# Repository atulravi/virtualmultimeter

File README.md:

# Virtual Voltmeter

A RPI Pico and/or Arduino and Python based ecosystem that will make a virtual voltmeter appear on screen that updates real time and can be used by streamers  who wish to show voltages on the screen as well. 

Best Suited for hardware development streamers and content creators. 

The voltmeter cannot read reverse polarity and voltages >25 volts right now because of the resistor divider used. Feel free to hack at the device and code if ambitious. I have used the arduino based voltage detector modules that have a 30K and 7.5K resistor ladder.

# Hardware.
- Upload code to your favorite dev board with Serial communication capabilities. (code in /hardware)
(Tested with Arduino and RPI Pico)
- Connect the parts as described in the schematic in the /hardware folder. 
- Fit in enclosure that you can 3d print (files provided for 2 styles in /hardware )
- Enjoy. 
- Download the 3D Files either from the folder or from printables: https://www.printables.com/model/497685-voltmeter-with-a-pi-pico-that-casts-the-data-to-a-

# Software
- Download the setup.exe file from the v1.0.0 Release. (Check releases tab.)
- Finish the setup (Don't worry. Does not contain any viruses. Just python code that scans the serial port to give a o/p)
- In the startup page, type the com port the voltmeter is connected to as is (eg: COM3 (or) com3)
- Enjoy

# Setting up streaming with software
- (Tested with OBS only)
- Start the voltameter software. 
- Start OBS.
- Add a source
- Add a window capture
- Choose the virtual multimeter from the dropdown
- [scanning.exe]: vIRTUAL MULTIMETER ESCcrasci
- After setting it at the posistion of choice
- Right click on the multimeter scene in OBS and presws on filters
- Press on the + and add chroma key
- Choose custom key colour type
- Select colour and add HTML code #00FFFF
- Once done, save and you are good to go. 
- It will look somewhat like this

SEE VIDEO BELOW FOR COMPLETE SETUP

https://github.com/atulravi/virtualmultimeter/assets/70395057/c0b2f832-0102-4875-b9c9-df2db2375dfc

# Platform

# Device pictures:
Please note that the inline socket version that can be directly plugged into a multimeter is still in development and will be released soon. Until then, either frankenstien it in the multimeter of your choice, or add a 7 segment display and use it as a seperate device.
- PostBox enclosure type

# Frankenstiend in to a DMM

(BEWARE. IF YOU RUIN YOUR DMM, I TAKE NO RESPONSIBILITY. RISKS ARE INVOLVED WITH OSSH)

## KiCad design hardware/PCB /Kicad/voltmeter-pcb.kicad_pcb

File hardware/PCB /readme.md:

Note that these PCBs are not compatible with the 3D Enclosures provided. Do keep that in mind.

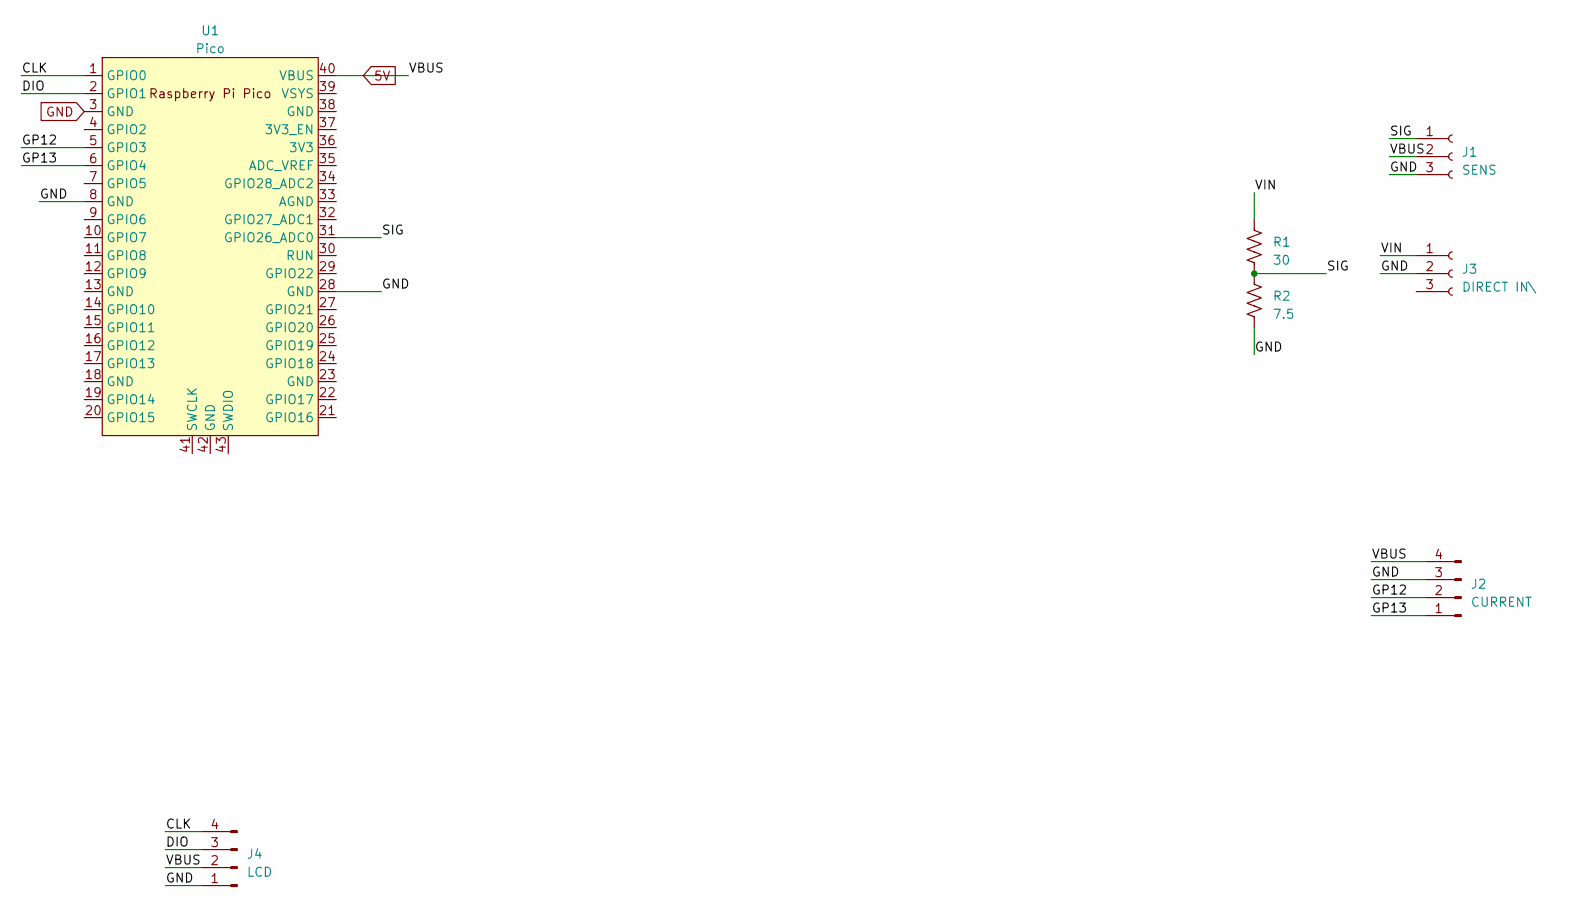
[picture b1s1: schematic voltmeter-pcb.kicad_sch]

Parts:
J1: SENS; PinSocket_1x03_P2.54mm_Vertical
J2: CURRENT; PinSocket_1x04_P2.54mm_Vertical
J3: DIRECT IN\; PinSocket_1x02_P2.54mm_Vertical
J4: LCD; PinSocket_1x04_P2.54mm_Vertical
R1: 30; R_1206_3216Metric
R2: 7.5; R_1206_3216Metric
U1: Pico; RPi_Pico_SMD_TH

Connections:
5V: J1.2, J2.4, J4.2, U1.40 (VBUS)
/CLK: J4.4, U1.1 (GPIO0)
/DIO: J4.3, U1.2 (GPIO1)
/GP12: J2.2, U1.5 (GPIO3)
/GP13: J2.1, U1.6 (GPIO4)
/SIG: J1.1, R1.2, R2.1, U1.31 (GPIO26_ADC0)
/VIN: J3.1, R1.1
GND: J1.3, J2.3, J3.2, J4.1, R2.2, U1.3 (GND), U1.8 (GND), U1.28 (GND)

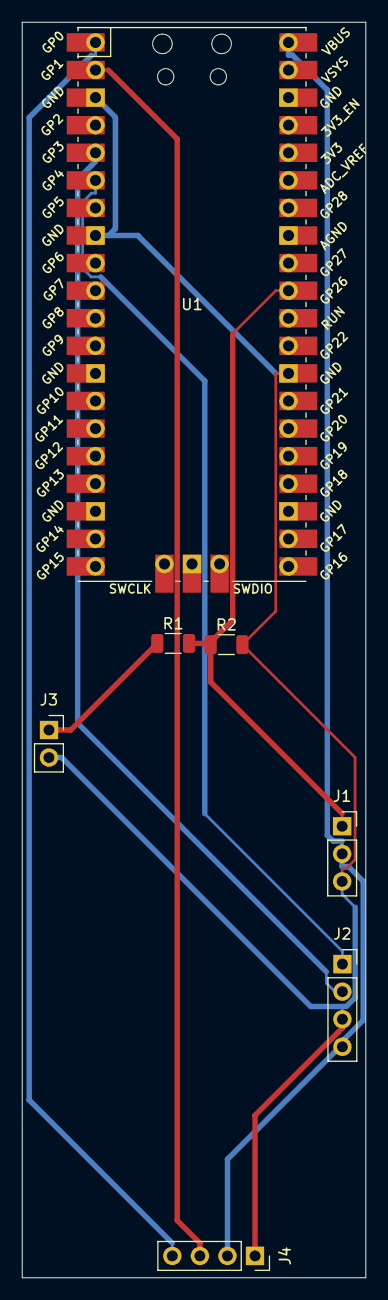
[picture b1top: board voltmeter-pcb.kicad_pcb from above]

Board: 2 copper layers, 31.6 x 115.6 mm, 7 parts (0 on the bottom side), 8 nets.

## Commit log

2023-05-30 Create 3D Files
2023-05-30 Create V1
2023-05-31 Add files via upload
    DESG7 FOnt rights belong to respective owners.
2023-06-03 Update README.md
    Pictures loading fixed
